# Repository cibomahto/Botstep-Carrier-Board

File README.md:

# Botstep Carrier Board
This is a carrier board for [botsteps](http://www.thingiverse.com/thing:16059), which can be used to connect up to four botsteps to Thing-O-Matic electronics.

# Attribution
All the part designs were lifted directly from the [Mightyboard](http://www.thingiverse.com/thing:16058) and [Thing-O-Matic](http://www.thingiverse.com/thing:4968) circuit designs.

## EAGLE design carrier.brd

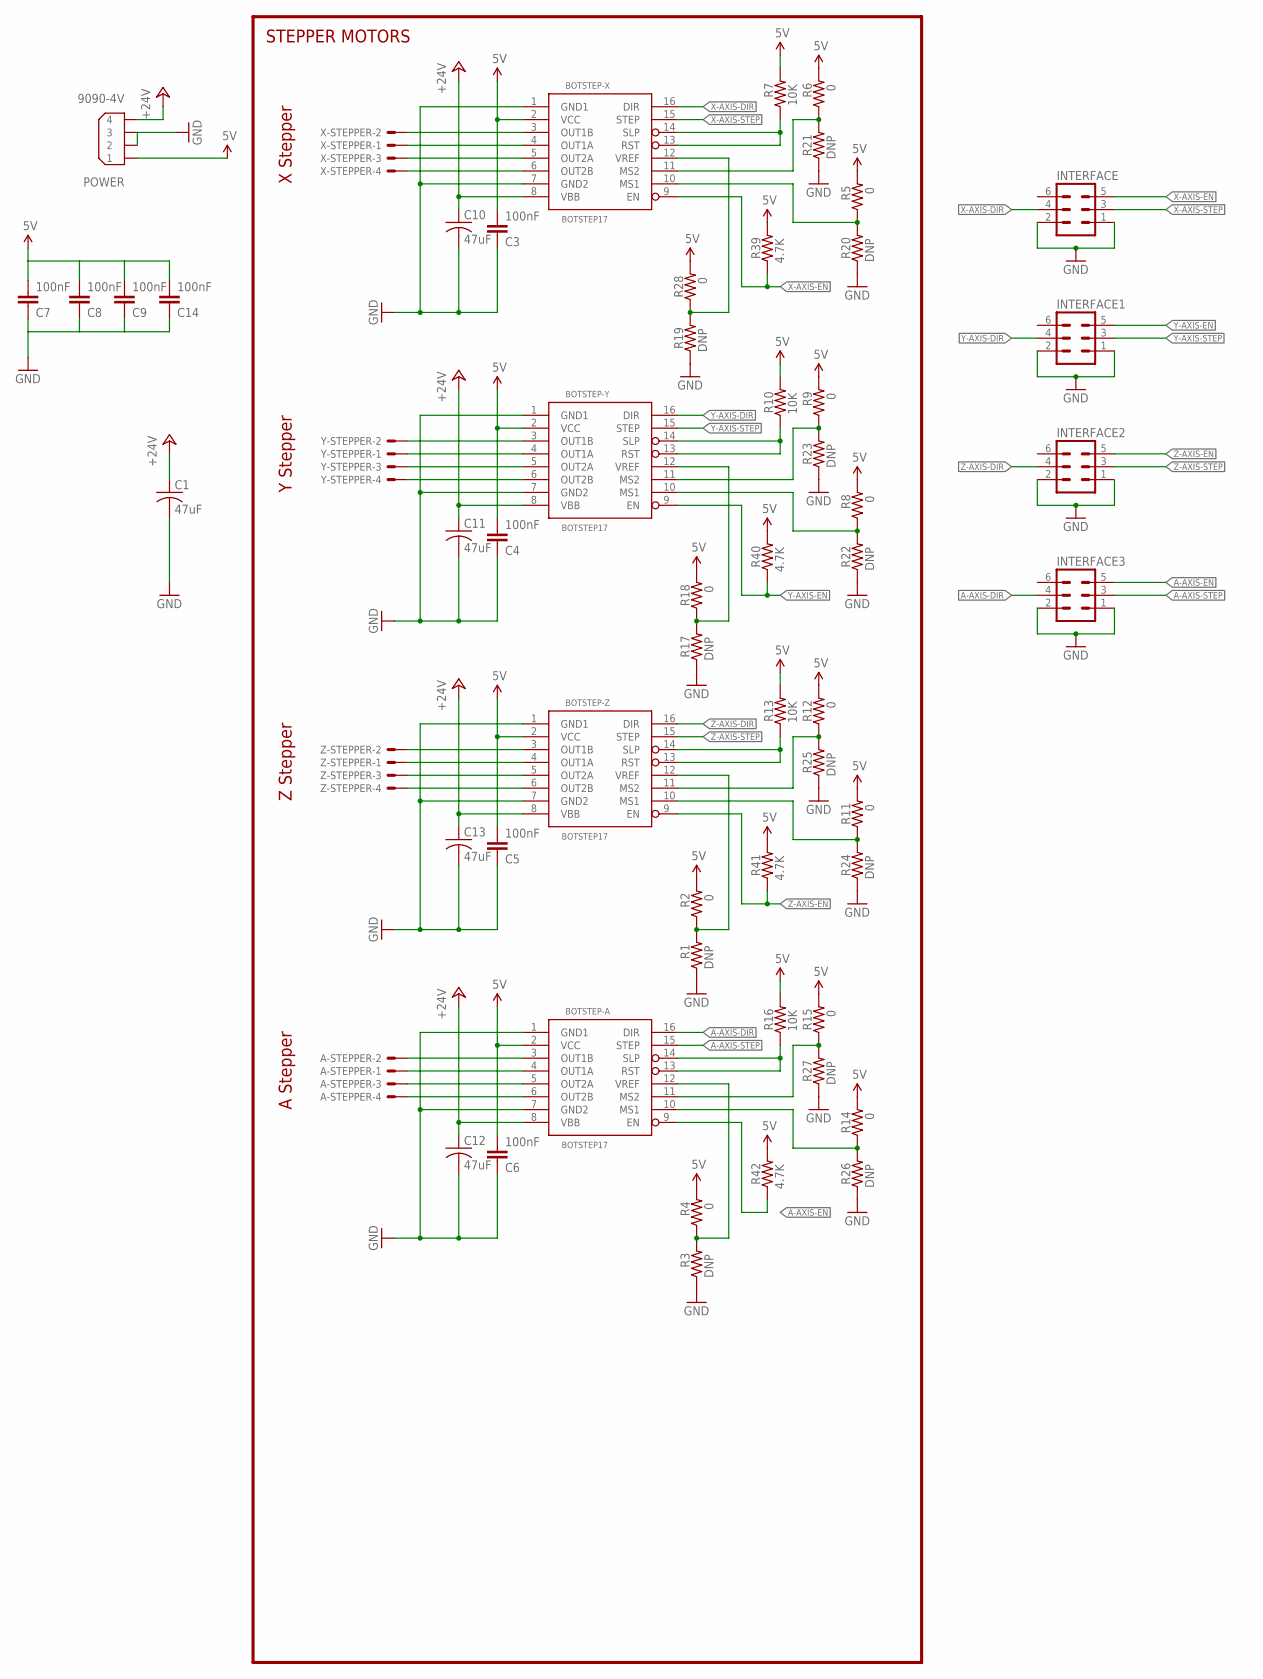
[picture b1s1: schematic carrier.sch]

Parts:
A-STEPPER: KK-156-4
BOTSTEP-A: BOTSTEP17; BOTSTEP17-INV
BOTSTEP-X: BOTSTEP17; BOTSTEP17-INV
BOTSTEP-Y: BOTSTEP17; BOTSTEP17-INV
BOTSTEP-Z: BOTSTEP17; BOTSTEP17-INV
C1, C10, C11, C12, C13: 47uF; C050-075X075
C3, C4, C5, C6, C7, C8, C9, C14: 100nF; CAP-PTH-5MM
INTERFACE, INTERFACE1, INTERFACE2, INTERFACE3: ML6
POWER: 9090-4V
R1, R3, R17, R19, R20, R21, R22, R23, R24, R25, R26, R27: DNP; AXIAL-0.3
R2, R4, R5, R6, R8, R9, R11, R12, R14, R15, R18, R28: 0; AXIAL-0.3
R7, R10, R13, R16: 10K; AXIAL-0.3
R39, R40, R41, R42: 4.7K; AXIAL-0.3
X-STEPPER: KK-156-4
Y-STEPPER: KK-156-4
Z-STEPPER: KK-156-4

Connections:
5V: BOTSTEP-A.2 (VCC), BOTSTEP-X.2 (VCC), BOTSTEP-Y.2 (VCC), BOTSTEP-Z.2 (VCC), C3.2, C4.2, C5.2, C6.2, C7.2, C8.2, C9.2, C14.2, POWER.1, R2.P$2 (2), R4.P$2 (2), R5.P$2 (2), R6.P$2 (2), R7.P$2 (2), R8.P$2 (2), R9.P$2 (2), R10.P$2 (2), R11.P$2 (2), R12.P$2 (2), R13.P$2 (2), R14.P$2 (2), R15.P$2 (2), R16.P$2 (2), R18.P$2 (2), R28.P$2 (2), R39.P$2 (2), R40.P$2 (2), R41.P$2 (2), R42.P$2 (2)
+24V: BOTSTEP-A.8 (VBB), BOTSTEP-X.8 (VBB), BOTSTEP-Y.8 (VBB), BOTSTEP-Z.8 (VBB), C1.1, C10.1, C11.1, C12.1, C13.1, POWER.4
A-AXIS-DIR: BOTSTEP-A.16 (DIR), INTERFACE3.4
A-AXIS-EN: BOTSTEP-A.9 (EN), INTERFACE3.5, R42.P$1 (1)
A-AXIS-STEP: BOTSTEP-A.15 (STEP), INTERFACE3.3
GND: BOTSTEP-A.1 (GND1), BOTSTEP-A.7 (GND2), BOTSTEP-X.1 (GND1), BOTSTEP-X.7 (GND2), BOTSTEP-Y.1 (GND1), BOTSTEP-Y.7 (GND2), BOTSTEP-Z.1 (GND1), BOTSTEP-Z.7 (GND2), C1.2, C3.1, C4.1, C5.1, C6.1, C7.1, C8.1, C9.1, C10.2, C11.2, C12.2, C13.2, C14.1, INTERFACE.1, INTERFACE.2, INTERFACE1.1, INTERFACE1.2, INTERFACE2.1, INTERFACE2.2, INTERFACE3.1, INTERFACE3.2, POWER.2, POWER.3, R1.P$1 (1), R3.P$1 (1), R17.P$1 (1), R19.P$1 (1), R20.P$1 (1), R21.P$1 (1), R22.P$1 (1), R23.P$1 (1), R24.P$1 (1), R25.P$1 (1), R26.P$1 (1), R27.P$1 (1)
unnamed: BOTSTEP-X.10 (MS1), R5.P$1 (1), R20.P$2 (2)
unnamed: BOTSTEP-X.13 (RST), BOTSTEP-X.14 (SLP), R7.P$1 (1)
unnamed: BOTSTEP-X.12 (VREF), R19.P$2 (2), R28.P$1 (1)
unnamed: BOTSTEP-X.11 (MS2), R6.P$1 (1), R21.P$2 (2)
unnamed: BOTSTEP-Y.13 (RST), BOTSTEP-Y.14 (SLP), R10.P$1 (1)
unnamed: BOTSTEP-X.3 (OUT1B), X-STEPPER.2
unnamed: BOTSTEP-X.4 (OUT1A), X-STEPPER.1
unnamed: BOTSTEP-X.5 (OUT2A), X-STEPPER.3
unnamed: BOTSTEP-X.6 (OUT2B), X-STEPPER.4
unnamed: BOTSTEP-Y.12 (VREF), R17.P$2 (2), R18.P$1 (1)
unnamed: BOTSTEP-Y.11 (MS2), R9.P$1 (1), R23.P$2 (2)
unnamed: BOTSTEP-Y.3 (OUT1B), Y-STEPPER.2
unnamed: BOTSTEP-Y.4 (OUT1A), Y-STEPPER.1
unnamed: BOTSTEP-Y.5 (OUT2A), Y-STEPPER.3
unnamed: BOTSTEP-Y.6 (OUT2B), Y-STEPPER.4
unnamed: BOTSTEP-Y.10 (MS1), R8.P$1 (1), R22.P$2 (2)
unnamed: BOTSTEP-Z.13 (RST), BOTSTEP-Z.14 (SLP), R13.P$1 (1)
unnamed: BOTSTEP-Z.12 (VREF), R1.P$2 (2), R2.P$1 (1)
unnamed: BOTSTEP-Z.11 (MS2), R12.P$1 (1), R25.P$2 (2)
unnamed: BOTSTEP-Z.3 (OUT1B), Z-STEPPER.2
unnamed: BOTSTEP-Z.4 (OUT1A), Z-STEPPER.1
unnamed: BOTSTEP-Z.5 (OUT2A), Z-STEPPER.3
unnamed: BOTSTEP-Z.6 (OUT2B), Z-STEPPER.4
unnamed: BOTSTEP-Z.10 (MS1), R11.P$1 (1), R24.P$2 (2)
unnamed: BOTSTEP-A.13 (RST), BOTSTEP-A.14 (SLP), R16.P$1 (1)
unnamed: BOTSTEP-A.12 (VREF), R3.P$2 (2), R4.P$1 (1)
unnamed: BOTSTEP-A.11 (MS2), R15.P$1 (1), R27.P$2 (2)
unnamed: A-STEPPER.2, BOTSTEP-A.3 (OUT1B)
unnamed: A-STEPPER.1, BOTSTEP-A.4 (OUT1A)
unnamed: A-STEPPER.3, BOTSTEP-A.5 (OUT2A)
unnamed: A-STEPPER.4, BOTSTEP-A.6 (OUT2B)
unnamed: BOTSTEP-A.10 (MS1), R14.P$1 (1), R26.P$2 (2)
X-AXIS-DIR: BOTSTEP-X.16 (DIR), INTERFACE.4
X-AXIS-EN: BOTSTEP-X.9 (EN), INTERFACE.5, R39.P$1 (1)
X-AXIS-STEP: BOTSTEP-X.15 (STEP), INTERFACE.3
Y-AXIS-DIR: BOTSTEP-Y.16 (DIR), INTERFACE1.4
Y-AXIS-EN: BOTSTEP-Y.9 (EN), INTERFACE1.5, R40.P$1 (1)
Y-AXIS-STEP: BOTSTEP-Y.15 (STEP), INTERFACE1.3
Z-AXIS-DIR: BOTSTEP-Z.16 (DIR), INTERFACE2.4
Z-AXIS-EN: BOTSTEP-Z.9 (EN), INTERFACE2.5, R41.P$1 (1)
Z-AXIS-STEP: BOTSTEP-Z.15 (STEP), INTERFACE2.3

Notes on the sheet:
X Stepper
STEPPER MOTORS
Y Stepper
Z Stepper
A Stepper

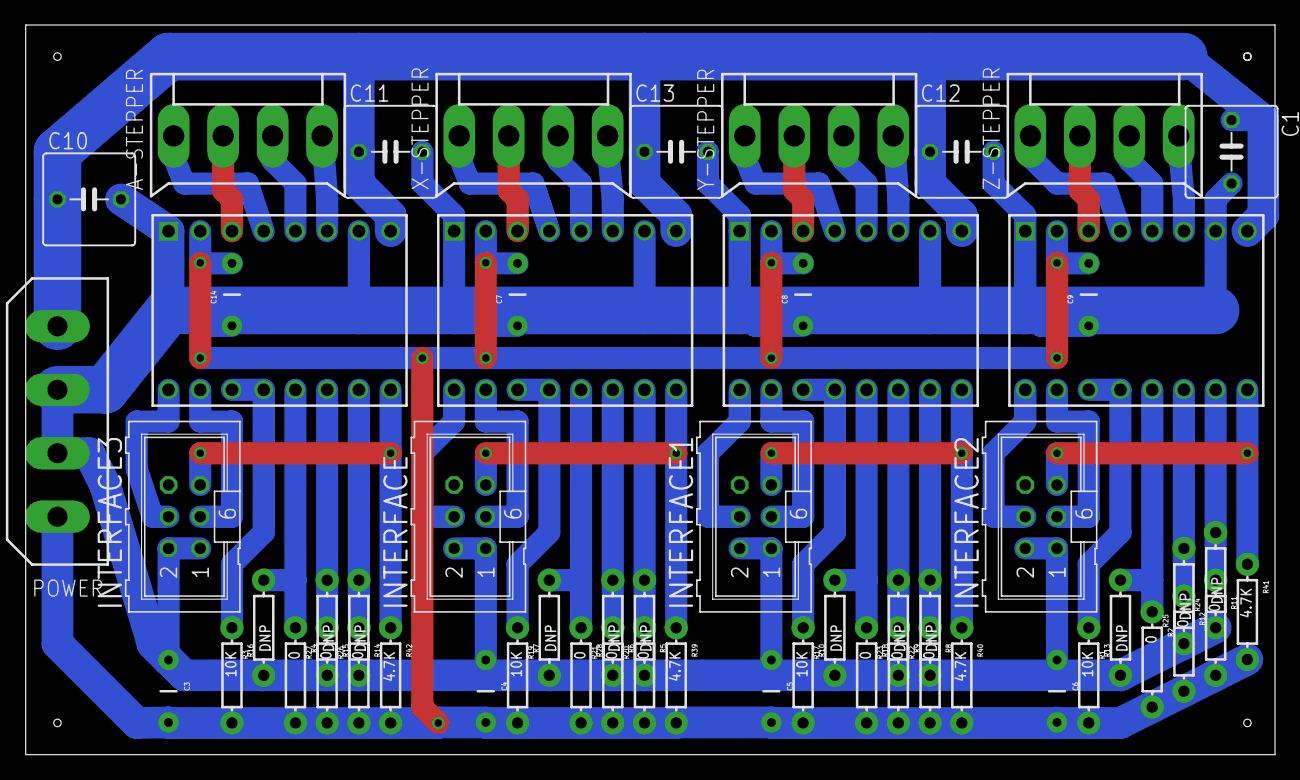
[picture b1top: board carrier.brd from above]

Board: 2 copper layers, 100.0 x 58.4 mm, 58 parts (0 on the bottom side), 47 nets.

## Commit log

2012-05-03 Initial version: it's a mightyboard! Get to the chopping!
2012-05-04 Designed! Routed! Time to build!
2012-06-21 add readme.
2012-06-27 Latest version?
2012-06-27 Cleanup
